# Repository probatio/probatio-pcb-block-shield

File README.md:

# probatio-pcb-block-shield
An arduino pro mini/micro shield for probatio blocks

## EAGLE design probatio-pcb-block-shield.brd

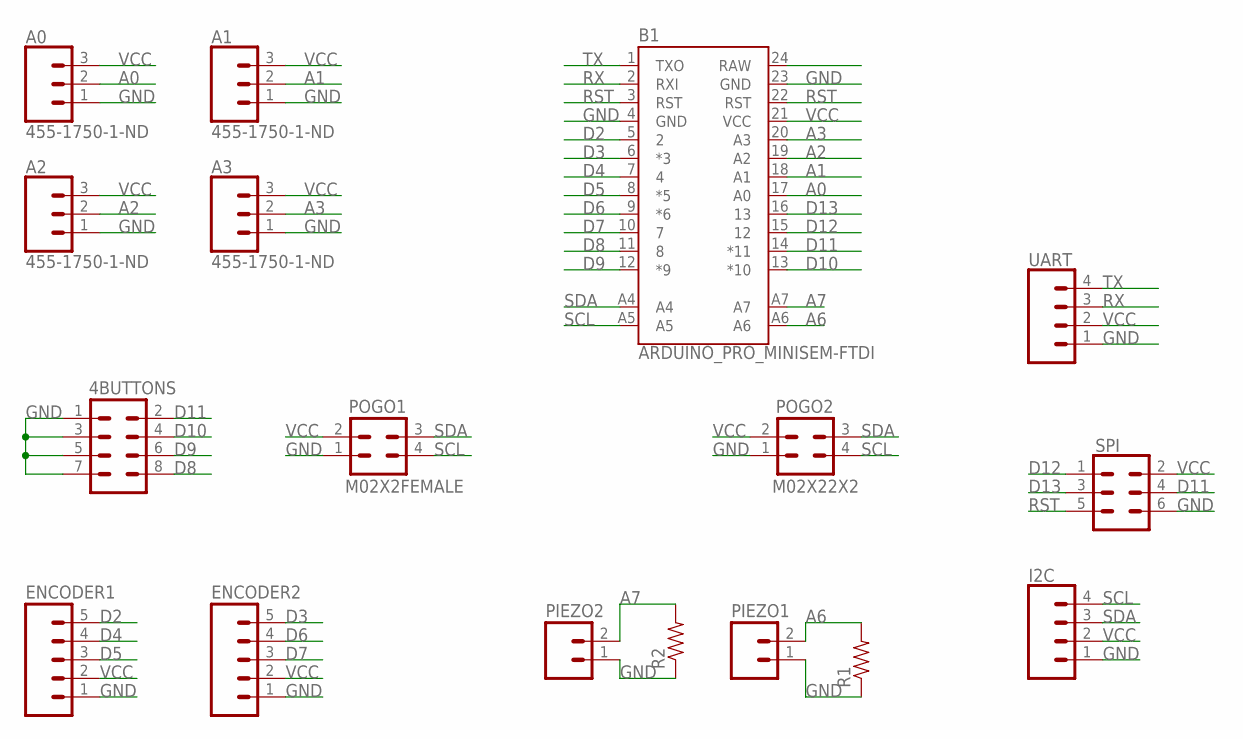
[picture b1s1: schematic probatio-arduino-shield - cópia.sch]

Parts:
4BUTTONS: M04X2; 2X4
A0, A1, A2, A3: 455-1750-1-ND; 1X03
B1: ARDUINO_PRO_MINISEM-FTDI; ARDUINO_PRO_MINI_S/FTDI
ENCODER1, ENCODER2: M05PTH; 1X05
I2C: CONN_04PTH; 1X04
PIEZO1, PIEZO2: M02PTH; 1X02
POGO1: M02X2FEMALE; 2X2INV
POGO2: M02X22X2; 2X2
R1, R2: RESISTORPTH-1/4W; AXIAL-0.4
SPI: CONN_03X2FEMALE; 2X3
UART: CONN_04PTH; 1X04

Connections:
A0: A0.2, B1.17 (A0)
A1: A1.2, B1.18 (A1)
A2: A2.2, B1.19 (A2)
A3: A3.2, B1.20 (A3)
A6: B1.A6, PIEZO1.2, R1.P$2 (2)
A7: B1.A7, PIEZO2.2, R2.P$2 (2)
D2: B1.5 (2), ENCODER1.5
D3: B1.6 (*3), ENCODER2.5
D4: B1.7 (4), ENCODER1.4
D5: B1.8 (*5), ENCODER1.3
D6: B1.9 (*6), ENCODER2.4
D7: B1.10 (7), ENCODER2.3
D8: 4BUTTONS.8, B1.11 (8)
D9: 4BUTTONS.6, B1.12 (*9)
D10: 4BUTTONS.4, B1.13 (*10)
D11: 4BUTTONS.2, B1.14 (*11), SPI.4
D12: B1.15 (12), SPI.1
D13: B1.16 (13), SPI.3
GND: 4BUTTONS.1, 4BUTTONS.3, 4BUTTONS.5, 4BUTTONS.7, A0.1, A1.1, A2.1, A3.1, B1.4 (GND), B1.23 (GND), ENCODER1.1, ENCODER2.1, I2C.1, PIEZO1.1, PIEZO2.1, POGO1.1, POGO2.1, R1.P$1 (1), R2.P$1 (1), SPI.6, UART.1
RST: B1.3 (RST), B1.22 (RST), SPI.5
RX: B1.2 (RXI), UART.3
SCL: B1.A5, I2C.4, POGO1.4, POGO2.4
SDA: B1.A4, I2C.3, POGO1.3, POGO2.3
TX: B1.1 (TXO), UART.4
VCC: A0.3, A1.3, A2.3, A3.3, B1.21 (VCC), ENCODER1.2, ENCODER2.2, I2C.2, POGO1.2, POGO2.2, SPI.2, UART.2

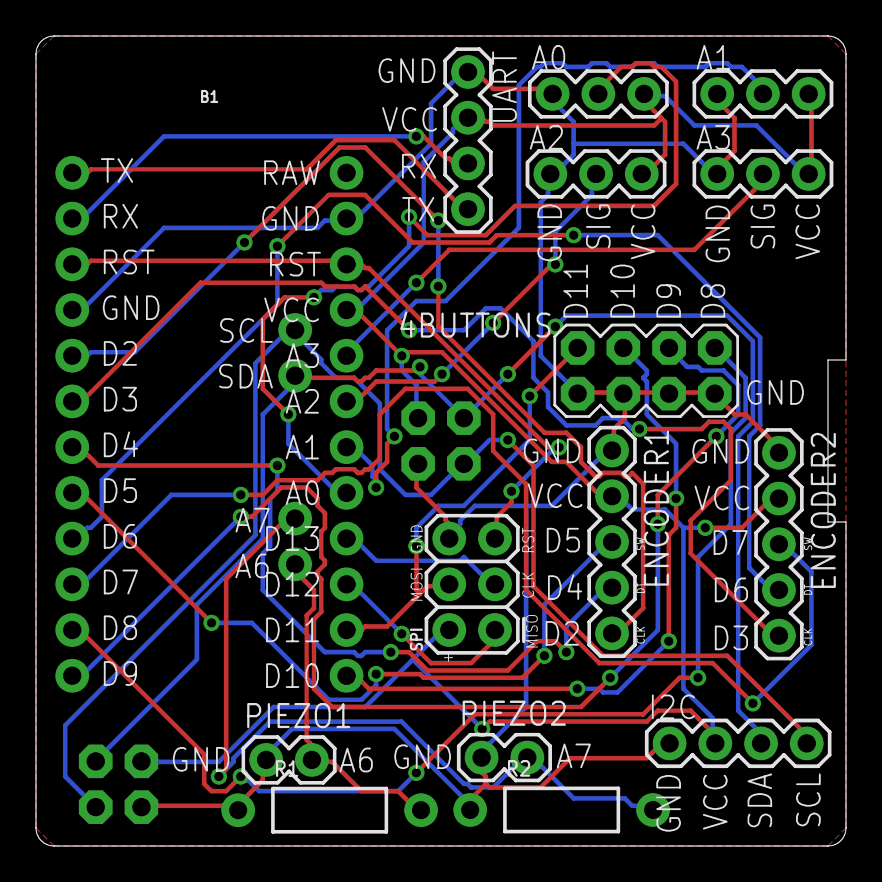
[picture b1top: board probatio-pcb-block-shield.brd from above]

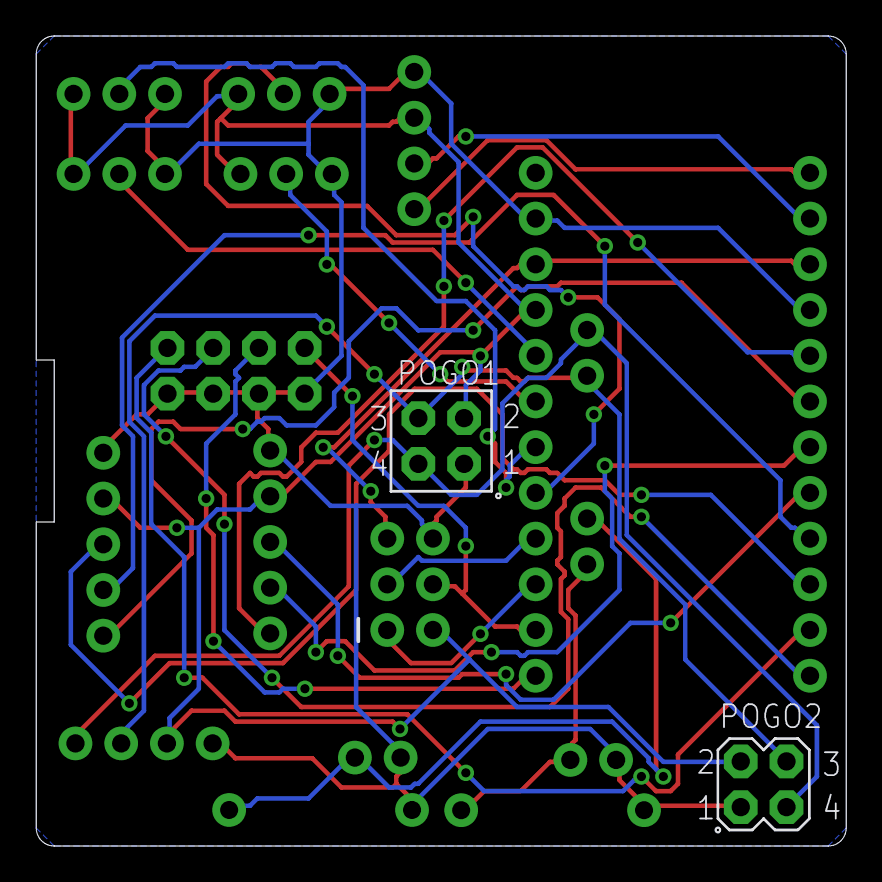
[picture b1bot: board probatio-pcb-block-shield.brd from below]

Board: 2 copper layers, 45.0 x 45.0 mm, 17 parts (2 on the bottom side), 25 nets.

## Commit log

2021-02-25 pcb for validation
2021-02-25 changed file names
